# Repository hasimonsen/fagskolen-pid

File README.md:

# 🌡️ Temperaturregulator med PID-kontroll
**Fagskoleprosjekt – Høst 2025**

Et semesterprosjekt ved [Fagskolen i Rogaland] for å utvikle et komplett system for **temperaturregulering basert på PID-kontroll**.  
Systemet består av et egendesignet PCB med innebygd varmesløyfe, temperatursensor og mikrokontroller (ESP32 med MicroPython).  
Prosjektet demonstrerer hvordan PID-regulering kan stabilisere temperatur i et tregt system med ytre forstyrrelser, som f.eks. vifte eller varmelekkasje.

---

## 🧠 Prosjektbeskrivelse

Prosjektet kombinerer **teori, simulering og praktisk implementering** for å bygge et fysisk system som kan:
- Regulere temperatur ved hjelp av P-, PI- og PID-algoritmer  
- Vise sanntidsdata via **webgrensesnitt** (Web UI)  
- Samhandle lokalt via **LCD-skjerm, knapper og vribrytere**  
- Logge temperaturforløp og PID-respons  
- Sammenlignes med simulering i **MATLAB/Simulink**

---

## ⚙️ Systemkomponenter

| Komponent | Beskrivelse |
|------------|-------------|
| **ESP32 (MicroPython)** | Mikrokontroller som kjører PID-algoritmen |
| **PCB med varmesløyfe** | Integrert varmeelement og temperatursensor |
| **Strømforsyning** | Ekstern 5–12 V forsyning for stabil drift |
| **Vifte / forstyrrelse** | Simulerer kjøling eller ekstern påvirkning |
| **Webportal (UI)** | Sanntidsgraf, parameterjustering og datalogging |
| **MATLAB/Simulink** | Brukt til simulering, tuning og analyse av PID-oppsett |

---

🧩 Mål og læringsutbytte

- Forstå praktisk bruk av PID-regulering i termiske systemer  
- Lære tuningmetoder (manuell og Ziegler–Nichols)  
- Sammenligne simulert og fysisk respons  
- Mestre bruk av GitHub til samarbeid og dokumentasjon  
- Koble teori (modellering) og praksis (implementering)

---

## 🗂️ Mappestruktur

```

fagskolen-pid/
│
├── pcb/                → PCB-design, komponentliste og skjema
├── code/               → MicroPython-kode for PID-regulering
├── webui/              → Frontend-filer for Web UI
├── matlab/             → Simuleringer og analyser
├── docs/               → Rapport, presentasjon og bilder
└── README.md           → Prosjektbeskrivelse (denne filen)

````

---

## 🧰 Installasjon og oppsett

## 🧪 Testing og simulering

* MATLAB/Simulink brukes til å simulere varmesystemets treghet og PID-respons.
* Faktiske målinger fra PCB kobles inn via UART eller WiFi.
* Temperaturdata logges og sammenlignes i grafer.

---

## 📜 Lisens

Dette prosjektet er lisensiert under [MIT License](LICENSE).

---

© 2025 – Fagskolen i Viken
Prosjektgruppe: Håkon Hjertnes Simonsen, Stian Emil Johansen, Francis Billy Rath

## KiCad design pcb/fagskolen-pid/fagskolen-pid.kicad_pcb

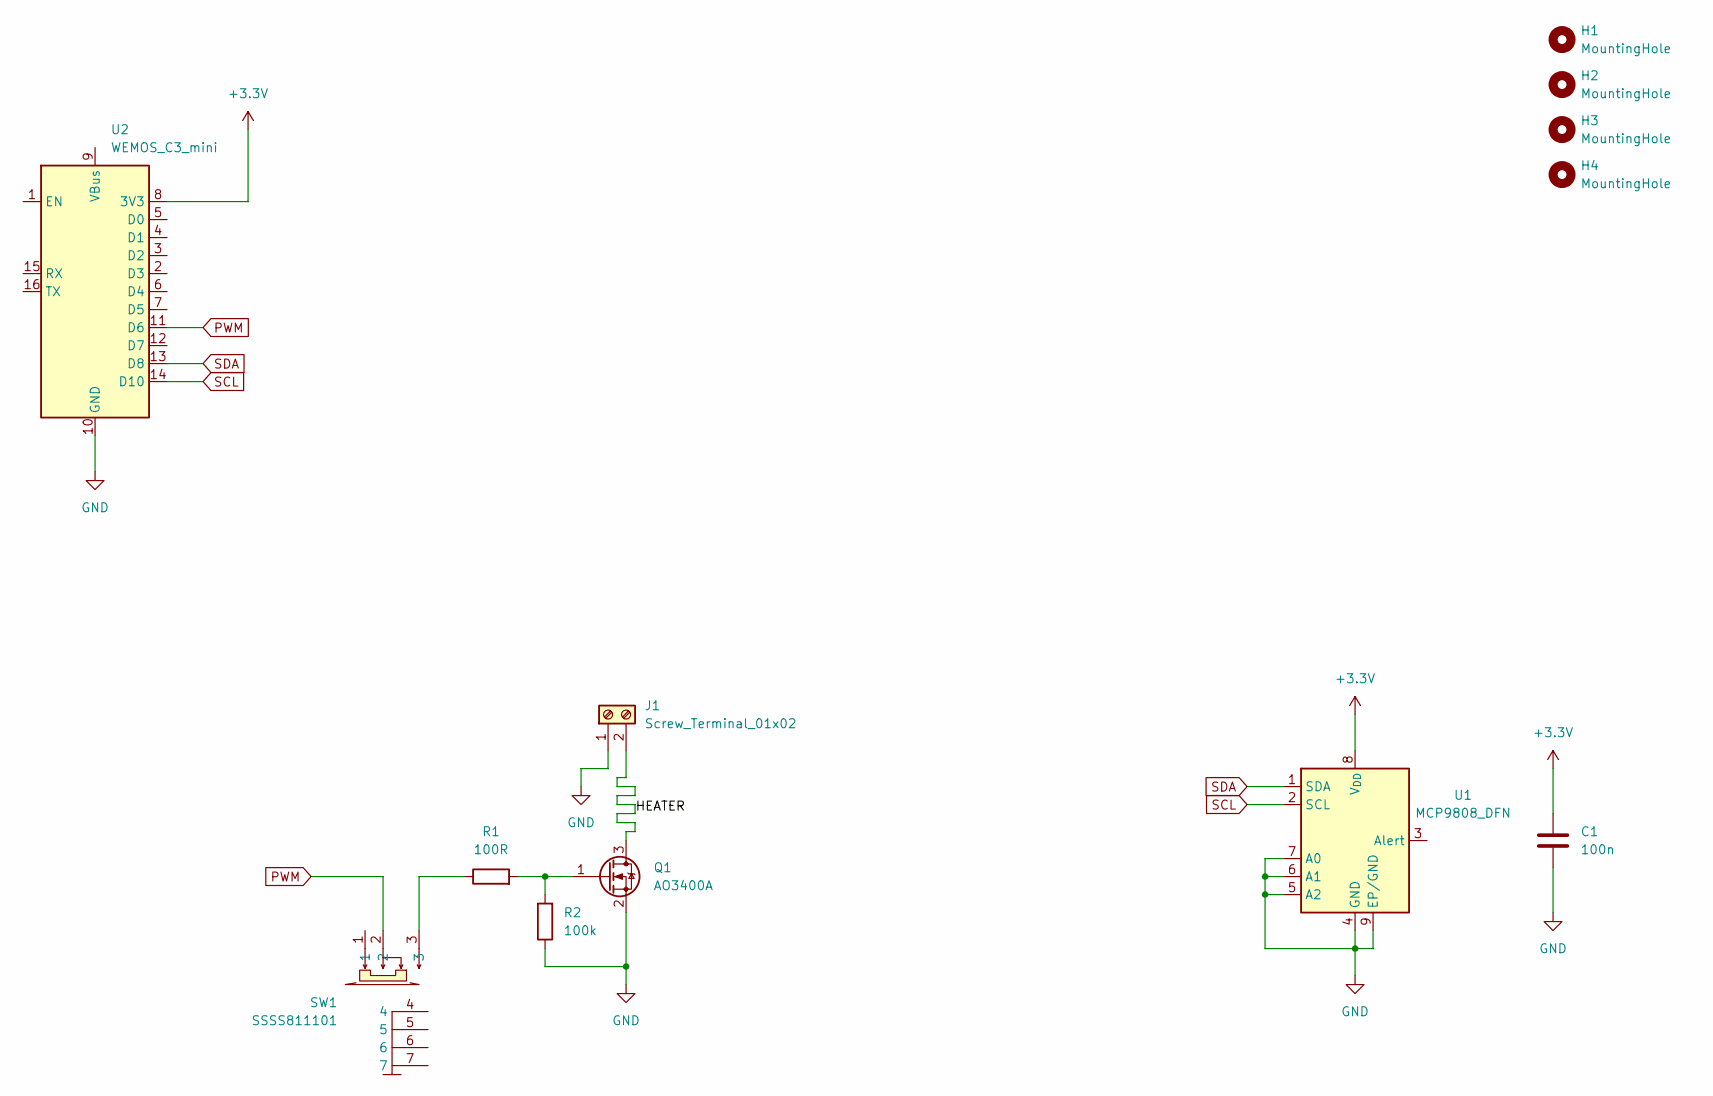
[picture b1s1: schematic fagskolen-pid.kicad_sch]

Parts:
C1: 100n; C_0603_1608Metric
H1, H2, H3, H4: MountingHole; MountingHole_3.2mm_M3_Pad_Via
J1: Screw_Terminal_01x02
Q1: AO3400A; SOT-23
R1: 100R; R_0805_2012Metric
R2: 100k; R_0805_2012Metric
SW1: SSSS811101; SW-SMD_SSSS811101; LCSC Part C109335
U1: MCP9808_DFN; DFN-8-1EP_3x2mm_P0.5mm_EP1.7x1.4mm
U2: WEMOS_C3_mini

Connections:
+3.3V: C1.1, U1.8 (V_{DD}), U2.8 (3V3)
/HEATER: J1.2, Q1.3 (D)
GND: C1.2, J1.1, Q1.2 (S), R2.1, U1.4 (GND), U1.5 (A2), U1.6 (A1), U1.7 (A0), U1.9 (EP/GND), U2.10 (GND)
unnamed: Q1.1 (G), R1.2, R2.2
unnamed: R1.1, SW1.3
PWM: SW1.2, U2.11 (D6)
SCL: U1.2 (SCL), U2.14 (D10)
SDA: U1.1 (SDA), U2.13 (D8)

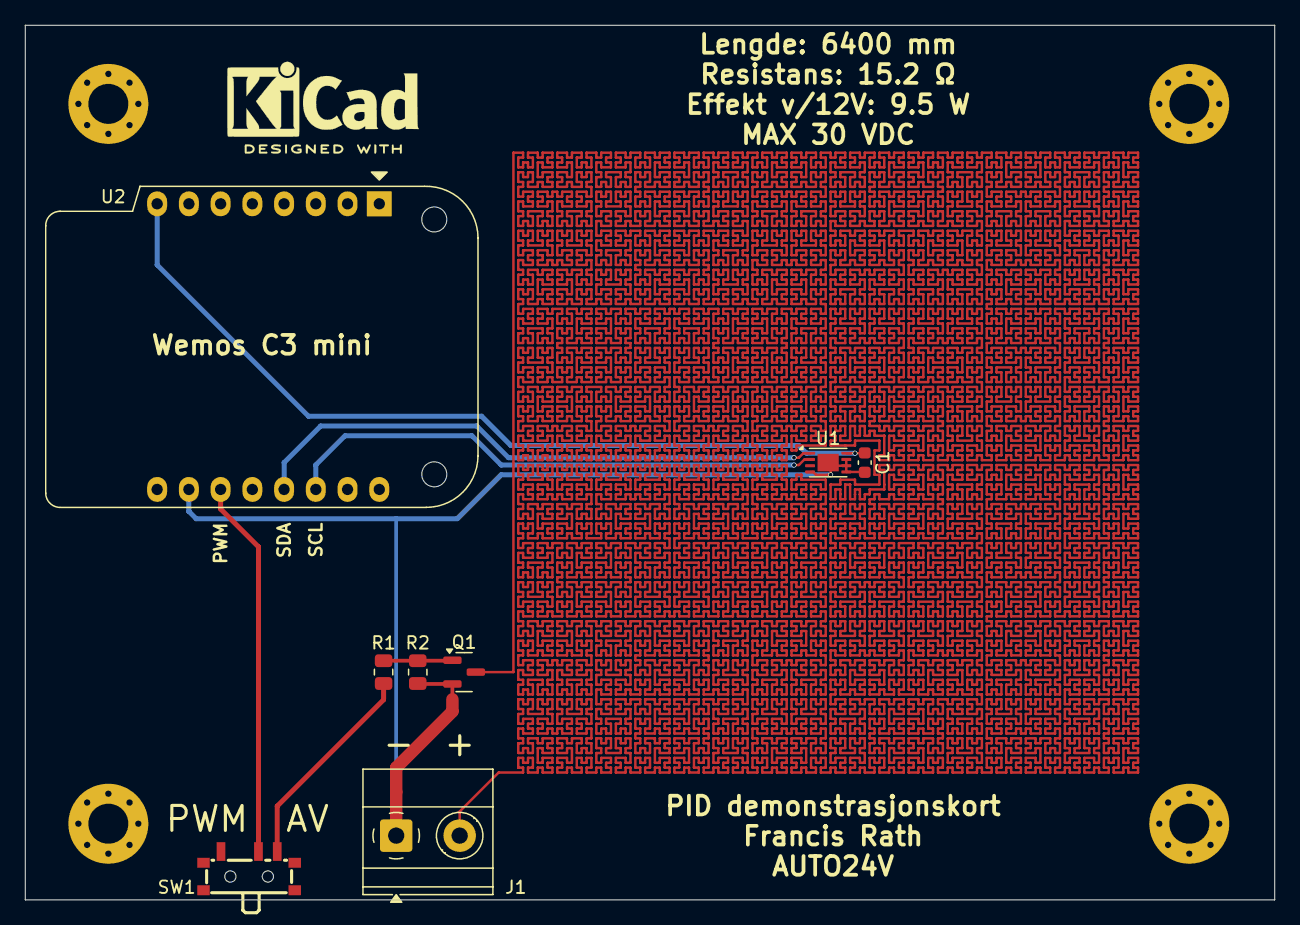
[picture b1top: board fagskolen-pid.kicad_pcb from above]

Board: 2 copper layers, 100.0 x 70.0 mm, 12 parts (0 on the bottom side), 8 nets.

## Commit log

2025-09-01 Kretskort-design som bestilt
2025-10-17 Revise README for temperature regulator project
    Updated README to provide detailed project description, components, goals, and structure.
2025-10-17 Create Semesterprosjekt beskrivelse.pdf
    Added new folder section for documents
2025-10-17 Update school name in project description
